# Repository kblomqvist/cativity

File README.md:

# Cativity

## SW Usage

nRF51 s110 softdevice is used by default (see `Makefile.project`), so at first you need to flash the softdevice binary:

```
make softdevice
```

The above command erase the chip and programs the softdevice binary appropriately. Now compile the user program and flash/upload it:

```
make
make upload
```

## Example/Test SW

Use `segger.py` script directly to flash `.bin` binaries.

### Proximity/RSSI test

```
export BUILD_PATH=./build
export JLINK_PATH=/usr/bin
python segger.py flash examples/ble_peripheral_proximity_nrf518222_xxaa_s110.bin 0x18000
```

## HW Errata
- ANT footprint
- QFN thermal pad paste mask too large
- Remove paste mask from programming pads
- 2u2 pad size too large, should be 0402

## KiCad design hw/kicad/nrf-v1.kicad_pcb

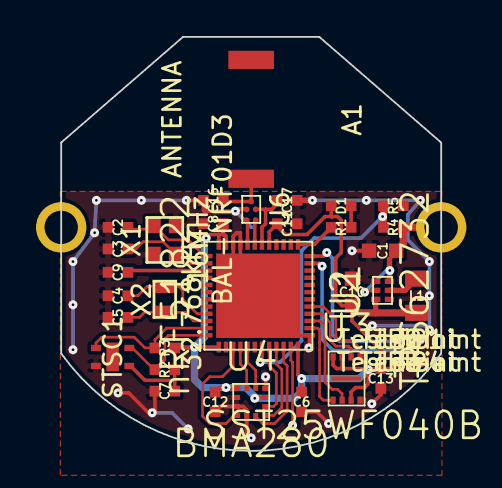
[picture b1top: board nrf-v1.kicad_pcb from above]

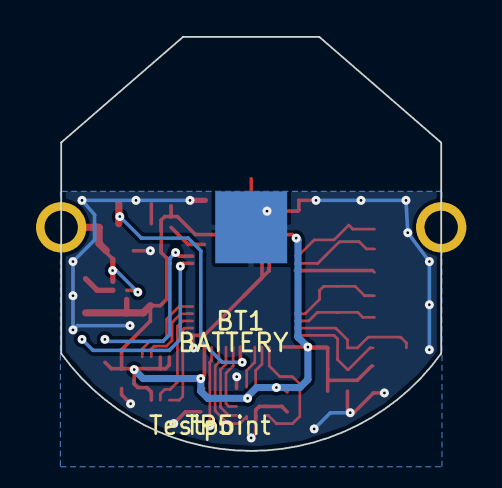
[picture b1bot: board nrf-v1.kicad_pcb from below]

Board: 2 copper layers, 21.1 x 23.0 mm, 37 parts (2 on the bottom side), 31 nets.

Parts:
A1: ANTENNA; AntennaFactor-ANT-2.4-CHP
BT1: BATTERY; Keystone-3003
C1, C10: 2u2; IPC-0603
C2, C3, C4, C5: 12p; IPC-0402
C6, C7, C9, C12, C13: 100n; IPC-0402
C8: 1n; IPC-0402
C11: 47n; IPC-0402
C16, C17: DNP; IPC-0402
D1: LED; IPC-0402
L1: INDUCTOR_SMALL; IPC-0805
R1: R; IPC-0402
R2, R3: 4k7; IPC-0402
R4: 100k; IPC-0402
R5: 120k; IPC-0402
TP1, TP2, TP3, TP4, TP5: Testpoint; TP_0.6
U1: TPS62732; TI-USON-6_(1.45x1.00)
U2: nRF51822; NordicSemi-QFN-48_(6.00x6.00)
U3: SST25WF040B; Microchip-USON-8_(2.00x3.00)
U4: BMA280; Bosch-LGA-12_(2.00x2.00)
U5: STSC1; Sensirion-DFN-4_(2.0x2.0)
U6: BAL-NRF01D3; ST-BGA-5_(1.50x1.00)
X1: 16MHz; Abracon-ABM10
X2: 32.768kHz; Abracon-ABS06

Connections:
+BATT: BT1.1, C1.1, R4.1, U1.3, U1.5
GND: BT1.2, C1.2, C2.2, C3.2, C4.2, C5.2, C6.2, C7.2, C8.2, C9.2, C10.2, C11.2, C12.2, C13.2, C16.2, C17.2, R5.2, TP4.1, U1.4, U2.13, U2.33, U2.34, U2.PAD, U3.4, U4.4, U4.8, U4.9, U4.11, U5.4, U6.A2, X1.2, X1.4
unnamed: A1.1, C16.1, U6.B1
unnamed: C2.1, U2.37, X1.1
unnamed: C3.1, U2.38, X1.3
unnamed: C4.1, U2.45, X2.1
unnamed: C5.1, U2.46, X2.2
unnamed: C9.1, U2.39
unnamed: C17.1, U2.30, U6.C2
unnamed: D1.2, R1.1
unnamed: L1.1, U1.2
unnamed: U2.31, U6.C3
unnamed: U2.32, U6.A3
VDD: C6.1, C7.1, C8.1, C10.1, C11.1, C12.1, C13.1, D1.1, L1.2, R2.1, R3.1, TP3.1, U1.6, U2.1, U2.12, U2.29, U2.35, U2.36, U3.3, U3.7, U3.8, U4.3, U4.7, U5.1
acc_int1: U2.5, U4.5
acc_int2: U2.4, U4.6
bootloader: TP5.1, U2.11
spi0_cs_n: U2.14, U3.1
spi0_miso: U2.15, U3.2
spi0_mosi: U2.17, U3.5
spi0_sck: U2.16, U3.6
spi1_cs_n: U2.3, U4.10
spi1_miso: U2.9, U4.1
spi1_mosi: U2.8, U4.2
spi1_sck: U2.10, U4.12
swclk: TP2.1, U2.24
swdio: TP1.1, U2.23
twi_scl: R2.2, U2.48, U5.2
twi_sda: R3.2, U2.47, U5.3
vbat_adc: R4.2, R5.1, U2.7
~led: R1.2, U2.25

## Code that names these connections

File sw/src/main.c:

#include <stdbool.h>
#include <stdint.h>
#include "nrf_delay.h"
#include "nrf_gpio.h"
#include "spi_master.h"

#include "twi_master.h"

#define SPI0_SCK  10
#define SPI0_MISO 9
#define SPI0_MOSI 11
#define SPI0_CSN  8

#define SPI1_SCK  6
#define SPI1_MISO 5
#define SPI1_MOSI 4
#define SPI1_CSN  30

bool stsc1_detect(void)
{
	const uint8_t address = 0x4A << 1;
	
	// check id
	uint8_t read_id_reg_cmd[2] = {0xef, 0xc8};
	uint8_t resp[3];
	
	if (!twi_master_transfer(address, read_id_reg_cmd, 2, TWI_ISSUE_STOP))
		return false; // failed
	
	if (!twi_master_transfer(address | TWI_READ_BIT, resp, sizeof(resp), TWI_ISSUE_STOP))
		return false; // failed
	
	if ((resp[1] & 0x3f) != 0b000111)
		return false; // wrong product code
	
	return true;
}

void spi_master_init(NRF_SPI_Type *base, int sck, int miso, int mosi)
{
	nrf_gpio_cfg_input(miso, NRF_GPIO_PIN_NOPULL);
	nrf_gpio_cfg_output(mosi);
	nrf_gpio_cfg_output(sck);

	set_spi_io(base, sck, miso, mosi);
	set_spi_mode(base, SPI_MODE_0);
	set_spi_clock(base, SPI_CLOCK_1M);
}

int main(void){
	nrf_gpio_cfg_output(17);
	
	twi_master_init();

	spi_master_init(NRF_SPI0, SPI0_SCK, SPI0_MISO, SPI0_MOSI);
	nrf_gpio_cfg_output(SPI0_CSN);

	spi_master_init(NRF_SPI1, SPI1_SCK, SPI1_MISO, SPI1_MOSI);
	nrf_gpio_cfg_output(SPI1_CSN);

	bool temp_present = stsc1_detect();

	while(1){
		nrf_gpio_pin_toggle(17);

		if (temp_present)
			nrf_delay_ms(500);
		else
			nrf_delay_ms(200);
	}
}

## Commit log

2015-02-18 Add KiCad design files
2015-02-18 Add datasheets
2015-02-18 Add AT45DB641E symbol
2015-02-18 Add SW template (with s110)
2015-02-18 gitignore sw/build/
2015-02-18 Add BMA280,SI7053 symbols
2015-02-18 Add TPS62732 symbol
2015-02-19 Add SST25WF040B symbol
2015-02-19 Add footprint library
2015-02-19 Initial layout
2015-02-19 Add coin cell holder datasheet
2015-02-19 Add crystals
2015-02-19 Change coin cell holder
    From 25mm to 20mm
2015-02-20 Component placement draft
2015-02-21 Updated coin cell holder
2015-02-22 Update nRF51 SDK to v7.2.0 (v6 is deprecated)
    - Also fix program starting address in segger.py to
    work with s110 v7.1.0. However, "make softdevice"
    doesn't seem to work -- had to program softdevice
    with nRF Studio (in Windows).
2015-02-24 Update schematics
2015-02-24 Add PCB shape
2015-02-25 Add mechanical design
    Seems like DS Mech does not support relative paths in design linking.
2015-02-28 Fix padding between pcb and enclosure
    Ready to pull enclosure
2015-02-28 Sketch bottom part of the enclosure
    Coin cell clip cannot be used for attaching the board to bottom side
    because otherwise it would become extremely thick.
2015-02-28 New mech sketches
2015-03-01 Add 0402 footprint
2015-03-01 Replace temp sensor
2015-03-08 Redrawn mech
    Fix filenaming later
2015-03-15 PCB ready for 1st review
2015-03-16 Add schematics as PDF
2015-03-16 Update schematic pdf
2015-03-16 Balun: enlarge solder paste openings
2015-03-16 Battery holder: enlarge annular rings
2015-03-16 Update layout
    - footprint updates
    - added gnd vias
    - polygon fills (max'd out)
2015-04-01 Add HW Errata
2015-04-03 Update NRF51 SDK to v8.0.0
    New SDK version now includes softdevice hex-files \o/
    Thus removing nrf51/sdk/ folder.
    Build system updated to work with latest SDK and softdevice
    version.
2015-04-03 Take out the garbage
2015-04-04 Add binary to quickly test proximity
2015-04-08 Update JLinkExe arguments
2015-04-08 Add STSC1 test
2015-04-18 Update gitignore
2015-04-19 Add C standard (gnu99)
    - nrf_delay.h doesn't compile with c99
2015-04-19 SPI helper functions
2015-04-19 Initialize SPI0 and 1
